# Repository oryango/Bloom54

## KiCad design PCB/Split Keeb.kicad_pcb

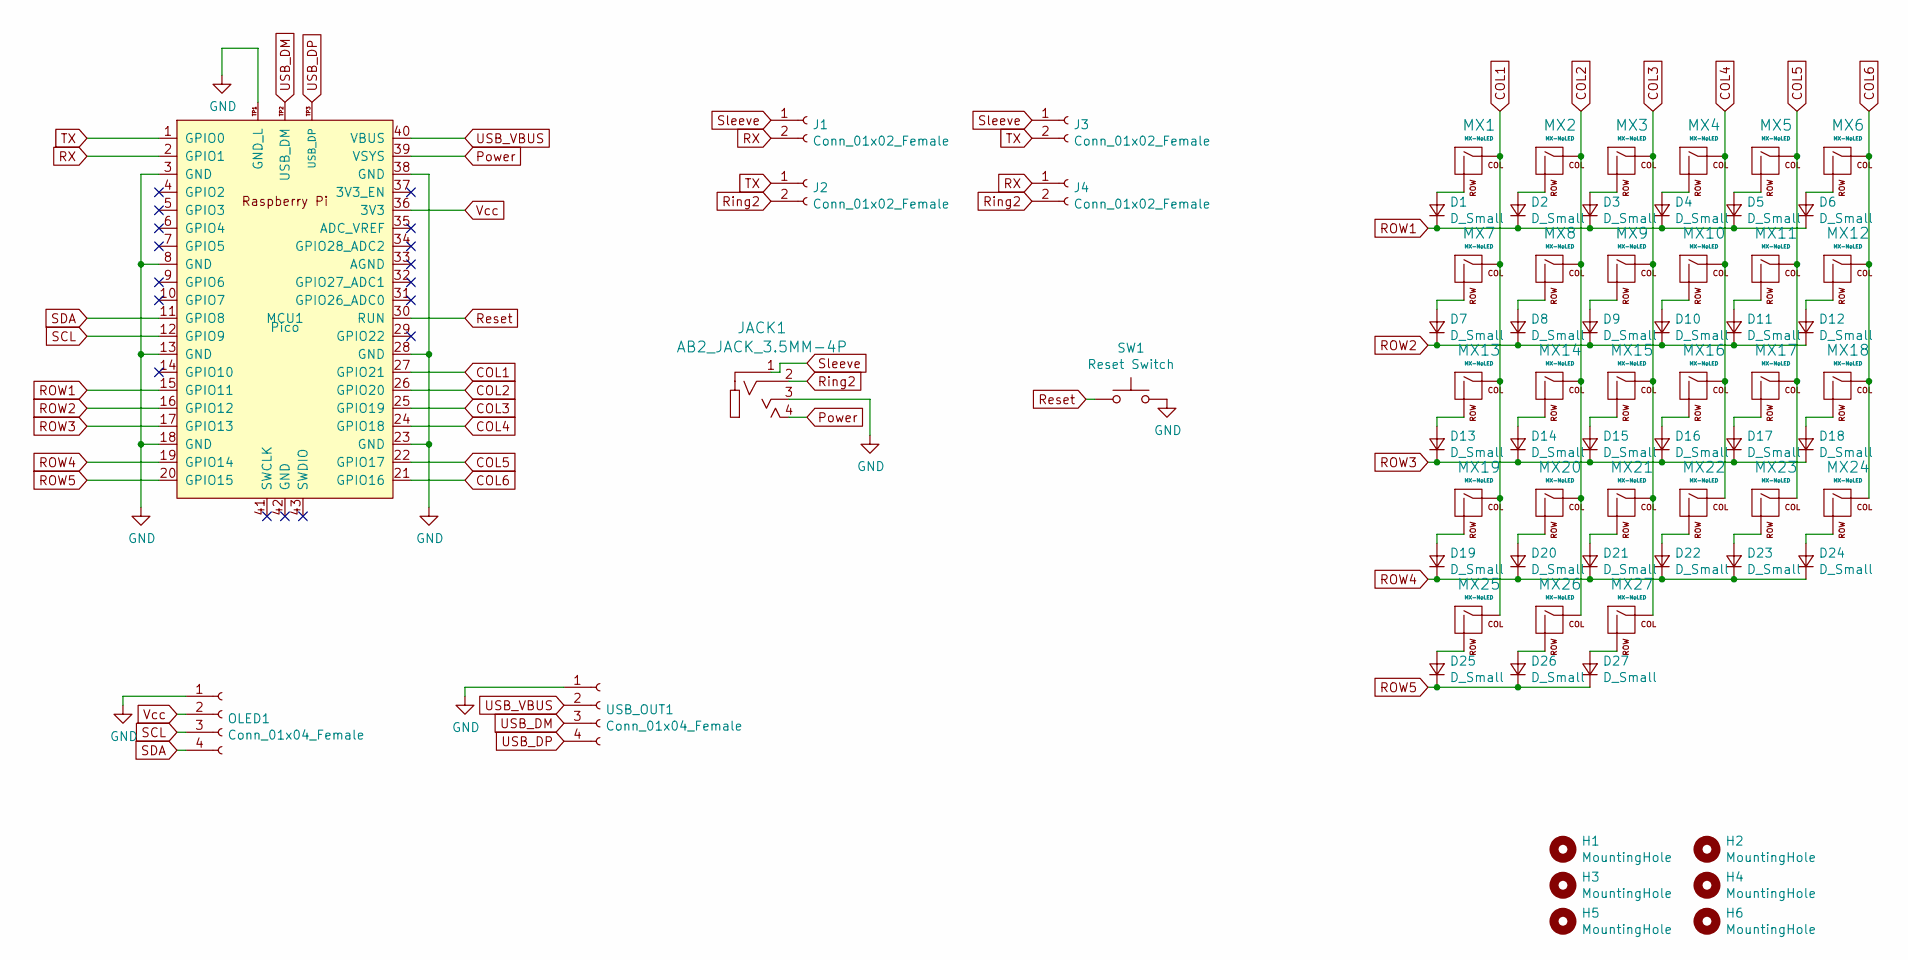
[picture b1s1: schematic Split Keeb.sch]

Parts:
D1, D2, D3, D4, D5, D6, D7, D8, D9, D10, D11, D12, D13, D14, D15, D16, D17, D18, D19, D20, D21, D22, D23, D24, D25, D26, D27: D_Small; D3_TH_SMD
H1, H2, H3, H4, H5, H6: MountingHole; MountingHole_3.2mm_M3
J1, J2: Conn_01x02_Female; SolderJumper-2_P1.3mm_Open_TrianglePad1.0x1.5mm
J3, J4: Conn_01x02_Female; SolderJumper-2_P1.3mm_Open_TrianglePad1.0x1.5mmBackCopper
JACK1: AB2_JACK_3.5MM-4P; 4P_RPi_AV_jack
MCU1: Pico; RPi_Pico_SMD_TH_Reversible
MX1, MX2, MX3, MX4, MX5, MX6, MX7, MX8, MX9, MX10, MX11, MX12, MX13, MX14, MX15, MX16, MX17, MX18, MX19, MX20, MX21, MX22, MX23, MX24, MX25, MX26, MX27: MX-NoLED; SW_MX_reversible
OLED1: Conn_01x04_Female; PinSocket_1x04_P2.54mm_Vertical
SW1: Reset Switch; SW_PUSH_6mm_H5mm
USB_OUT1: Conn_01x04_Female; PinSocket_1x04_P2.54mm_Vertical

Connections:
COL1: MCU1.27 (GPIO21), MX1.1 (COL), MX7.1 (COL), MX13.1 (COL), MX19.1 (COL), MX25.1 (COL)
COL2: MCU1.26 (GPIO20), MX2.1 (COL), MX8.1 (COL), MX14.1 (COL), MX20.1 (COL), MX26.1 (COL)
COL3: MCU1.25 (GPIO19), MX3.1 (COL), MX9.1 (COL), MX15.1 (COL), MX21.1 (COL), MX27.1 (COL)
COL4: MCU1.24 (GPIO18), MX4.1 (COL), MX10.1 (COL), MX16.1 (COL), MX22.1 (COL)
COL5: MCU1.22 (GPIO17), MX5.1 (COL), MX11.1 (COL), MX17.1 (COL), MX23.1 (COL)
COL6: MCU1.21 (GPIO16), MX6.1 (COL), MX12.1 (COL), MX18.1 (COL), MX24.1 (COL)
GND: JACK1.3, MCU1.3 (GND), MCU1.8 (GND), MCU1.13 (GND), MCU1.18 (GND), MCU1.23 (GND), MCU1.28 (GND), MCU1.38 (GND), MCU1.TP1 (GND_L), OLED1.1, SW1.2, USB_OUT1.1; also elsewhere on the board
unnamed: D1.2 (A), MX1.2 (ROW)
unnamed: D2.2 (A), MX2.2 (ROW)
unnamed: D3.2 (A), MX3.2 (ROW)
unnamed: D4.2 (A), MX4.2 (ROW)
unnamed: D5.2 (A), MX5.2 (ROW)
unnamed: D6.2 (A), MX6.2 (ROW)
unnamed: D7.2 (A), MX7.2 (ROW)
unnamed: D8.2 (A), MX8.2 (ROW)
unnamed: D9.2 (A), MX9.2 (ROW)
unnamed: D10.2 (A), MX10.2 (ROW)
unnamed: D11.2 (A), MX11.2 (ROW)
unnamed: D12.2 (A), MX12.2 (ROW)
unnamed: D13.2 (A), MX13.2 (ROW)
unnamed: D14.2 (A), MX14.2 (ROW)
unnamed: D15.2 (A), MX15.2 (ROW)
unnamed: D16.2 (A), MX16.2 (ROW)
unnamed: D17.2 (A), MX17.2 (ROW)
unnamed: D18.2 (A), MX18.2 (ROW)
unnamed: D19.2 (A), MX19.2 (ROW)
unnamed: D20.2 (A), MX20.2 (ROW)
unnamed: D21.2 (A), MX21.2 (ROW)
unnamed: D22.2 (A), MX22.2 (ROW)
unnamed: D23.2 (A), MX23.2 (ROW)
unnamed: D24.2 (A), MX24.2 (ROW)
unnamed: D25.2 (A), MX25.2 (ROW)
unnamed: D26.2 (A), MX26.2 (ROW)
unnamed: D27.2 (A), MX27.2 (ROW)
Power: JACK1.4, MCU1.39 (VSYS)
ROW1: D1.1 (K), D2.1 (K), D3.1 (K), D4.1 (K), D5.1 (K), D6.1 (K), MCU1.15 (GPIO11)
ROW2: D7.1 (K), D8.1 (K), D9.1 (K), D10.1 (K), D11.1 (K), D12.1 (K), MCU1.16 (GPIO12)
ROW3: D13.1 (K), D14.1 (K), D15.1 (K), D16.1 (K), D17.1 (K), D18.1 (K), MCU1.17 (GPIO13)
ROW4: D19.1 (K), D20.1 (K), D21.1 (K), D22.1 (K), D23.1 (K), D24.1 (K), MCU1.19 (GPIO14)
ROW5: D25.1 (K), D26.1 (K), D27.1 (K), MCU1.20 (GPIO15)
RX: J1.2, J4.1, MCU1.2 (GPIO1)
Reset: MCU1.30 (RUN), SW1.1; also elsewhere on the board
Ring2: J2.2, J4.2, JACK1.2
SCL: MCU1.12 (GPIO9), OLED1.3
SDA: MCU1.11 (GPIO8), OLED1.4
Sleeve: J1.1, J3.1, JACK1.1
TX: J2.1, J3.2, MCU1.1 (GPIO0)
USB_DM: MCU1.TP2 (USB_DM), USB_OUT1.3; also elsewhere on the board
USB_DP: MCU1.TP3 (USB_DP), USB_OUT1.4; also elsewhere on the board
USB_VBUS: MCU1.40 (VBUS), USB_OUT1.2; also elsewhere on the board
Vcc: MCU1.36 (3V3), OLED1.2

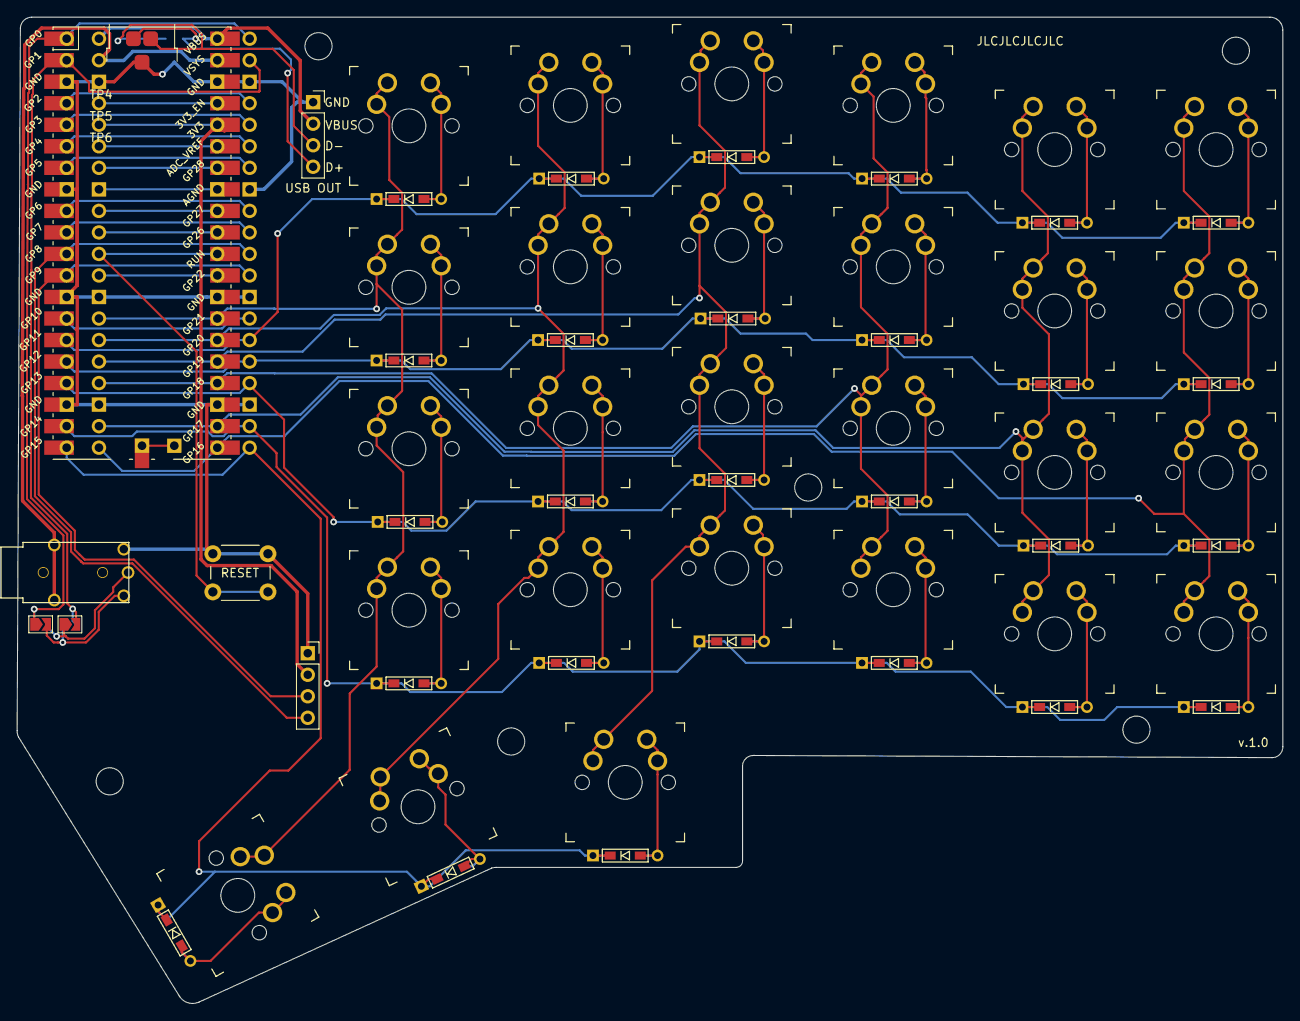
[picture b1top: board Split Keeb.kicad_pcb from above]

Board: 2 copper layers, 149.4 x 116.4 mm, 69 parts (0 on the bottom side), 51 nets.

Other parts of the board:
RESET: Reset Switch; SW_PUSH_6mm_H5mm
USB OUT: Conn_01x04_Female; PinSocket_1x04_P2.54mm_Vertical

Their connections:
GND: RESET.2, USB OUT.1; also elsewhere on the board
Reset: RESET.1; also elsewhere on the board
USB_DM: USB OUT.3; also elsewhere on the board
USB_DP: USB OUT.4; also elsewhere on the board
USB_VBUS: USB OUT.2; also elsewhere on the board

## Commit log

2022-02-15 File dump from local repo
2022-02-15 Deleted unnecessary files
